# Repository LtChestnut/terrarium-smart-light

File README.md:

# terrarium-smart-light

An ESP32-based smart grow light for terrariums: a compact 56 mm round board with components on one side with full-spectrum white LEDs for plant growth, addressable RGB LEDs for effects, and Wi-Fi control.

## Features (planned)
- Seeed Studio XIAO module soldered directly to the board (ESP32-C6 recommended for its on-board antenna; the S3 and C3 also fit)
- Dimmable, wide-angle (120°) warm white LEDs (ams OSRAM DURIS E 2835, 3000 K, CRI 90+) on a constant-current boost driver (Legend-Si LGS63032EP, flicker-free PWM dimming)
- Addressable RGB pixels (WS2812-compatible) for sunrise/sunset, moonlight and effects
- A separate USB-C power port (5 V, works with any 2–3 A USB-C charger). The firmware reads the charger's advertised current and limits brightness to match
- 4-layer PCB with every component on one side (the back sits flat on a heatsink). JLCPCB Economic assembly places all LCSC parts; only the XIAO is hand-soldered
- Day/night schedule with sunrise and sunset ramps, a web UI, OTA updates, and Home Assistant via MQTT

## Repository layout
| Folder | Contents |
|---|---|
| [docs/](docs/) | Design plan ([docs/plan.md](docs/plan.md)) and research notes ([docs/research/](docs/research/)) |
| [hardware/](hardware/) | KiCad project, BOM, fabrication outputs |
| [firmware/](firmware/) | PlatformIO project for the XIAO (ESP32-C6 primary, S3 supported) |
| [enclosure/](enclosure/) | Enclosure STEP files exported from Onshape |

## Mechanical design
The enclosure is designed in Onshape: [Terrarium Smart Light enclosure (Onshape)](https://cad.onshape.com/documents/52f2a238255e278aeea46164/w/27e2eabc0946d9f68195188c/e/e4bc6922c2e565c6999771c4). The Onshape document is the source of truth; the STEP files in [enclosure/](enclosure/) are exports of it, so re-export them after changing the design.

| File | Part |
|---|---|
| [enclosure/main_enclosure.step](enclosure/main_enclosure.step) | Main enclosure body |
| [enclosure/frosted_window.step](enclosure/frosted_window.step) | Frosted window over the LEDs |

The PCB model used in the assembly is [hardware/Terrarium Smart Light.step](hardware/Terrarium%20Smart%20Light.step), exported from KiCad with `kicad-cli pcb export step --subst-models --no-optimize-step`. It mounts with the four M3 holes on the board edge.

## Status
PCB v0.6 has been sent for manufacture (JLCPCB); bring-up and firmware testing follow once boards arrive. The enclosure is designed in Onshape. See [docs/plan.md](docs/plan.md) for the architecture, power budget, BOM and open decisions.

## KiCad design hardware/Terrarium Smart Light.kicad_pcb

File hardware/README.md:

# Hardware

KiCad 10 project: `Terrarium Smart Light.kicad_pro`

| File | Contents |
|---|---|
| `Terrarium Smart Light.kicad_sch` | Root sheet: four hierarchical sheets wired together |
| `power_input.kicad_sch` | USB-C power-only sink (J1, SHOU HAN TYPE-C 6P), CC Rd resistors, XIAO feed diode |
| `mcu.kicad_sch` | Seeed XIAO ESP32-C6 (U1) |
| `white_led_driver.kicad_sch` | LGS63032EP boost driver (OVP divider at 31 V), 16 × OSRAM DURIS E 2835 3000 K CRI 90 (2 parallel strings of 8), NTC |
| `rgb_leds.kicad_sch` | 6 × XINGLIGHT XL-5050RGBW-2812B-HM addressable RGB chain, 2N7002 data level shifter |
| `libs/Terrarium_Smart_Light.kicad_sym` | Project symbols: Seeed_XIAO_ESP32C6, LGS63032EP |
| `libs/Terrarium_Smart_Light.pretty` | Project footprints: XIAO-ESP32-C6-SMD_EdgePads, LED_OSRAM_DURIS_E_2835, USB_C_Receptacle_SHOUHAN_TYPE-C-6P (LED_Seoul_SunLike_S1S0-3030 kept, unused) |
| `libs/Terrarium_Smart_Light.3dshapes` | Simplified 3D model for the OSRAM 2835 |
| `resources/` | XIAO STEP model, J1 drawing, `datasheets/` (PDFs; markdown copies in `docs/datasheets`) |
| `bom/bom.csv` | Master BOM (with `LCSC Part #`) |
| `bom/jlcpcb_bom.csv` | Parts for JLCPCB Economic assembly (LCSC numbers) |
| `bom/digikey_bom_5x.csv` | Hand-soldered parts for 5 boards (U1 only) |
| `fabrication-toolkit-options.json` | Saved Fabrication-Toolkit plugin options |
| `production/` | Fabrication-Toolkit output. **Not in git**: regenerate it for every order (see below) |

Checks:

```
kicad-cli sch erc "Terrarium Smart Light.kicad_sch"
kicad-cli pcb drc --schematic-parity --refill-zones "Terrarium Smart Light.kicad_pcb"
kicad-cli sch export bom -o bom/bom.csv --fields "Reference,Value,Footprint,Manufacturer,MFG Part Number,Supplier,Supplier Part Number,${QUANTITY}" --group-by "Value,MFG Part Number" "Terrarium Smart Light.kicad_sch"
```

## Generating production files (JLCPCB, Fabrication-Toolkit)

The [Fabrication-Toolkit](https://github.com/bennymeg/Fabrication-Toolkit) plugin builds everything JLCPCB needs from the board. It takes the gerbers, drill files, BOM and pick-and-place data straight from the PCB. It reads the **`LCSC Part #`** field on each footprint; every JLCPCB-placed part has one, while U1 (the XIAO, hand-soldered) and H1–H4 (holes) don't.

### 1. Install the plugin (once)
1. Open KiCad and go to **Tools → Plugin and Content Manager**.
2. Search for **Fabrication Toolkit**, click **Install**, then **Apply Pending Changes**.
3. Restart the PCB editor. A Fabrication Toolkit button appears in its top toolbar. It's also under **Tools → External Plugins**.

### 2. Before generating
1. **Update the PCB from the schematic** (F8), so the footprint fields (`LCSC Part #`, values) are current.
2. **Refill all zones** (press B).
3. **Run DRC** with "Test for parity between PCB and schematic" ticked. It should report 0 errors and 0 unconnected items. Silkscreen warnings are optional fixes.
4. **Save the board.**

### 3. Generate
1. Click the **Fabrication Toolkit** button.
2. The options saved in `fabrication-toolkit-options.json` are already right for this board:
   - **Auto fill:** on (refills zones first).
   - **Auto translate:** on (applies the plugin's JLCPCB rotation corrections).
   - **Exclude DNP:** off.
   - **Extra layers:** none.
3. Click **Generate**. The output goes to `hardware/production/`:

| File | Use |
|---|---|
| `Terrarium_Smart_Light.zip` | Gerbers and drill files, for the PCB order |
| `bom.csv` | Assembly BOM (LCSC part numbers) |
| `positions.csv` | Pick-and-place (CPL) file |
| `designators.csv`, `netlist.ipc` | Reference files. The IPC netlist can be uploaded for JLCPCB's electrical test |

### 4. Order on jlcpcb.com
**PCB:** upload `Terrarium_Smart_Light.zip` and set:
- **Layers:** 4.
- **Thickness:** 1.6 mm.
- **Stack-up:** JLC04161H-7628, which the DRC rules assume.
- **Via covering:** tented is fine. The 4-layer vias aren't via-in-pad filled (that's only free on 6+ layers), so leave "via-in-pad" off.
- **Edge plating / castellated holes:** none. The M3 edge holes are non-plated, which is what makes the board eligible for Economic assembly.

**PCB Assembly:** choose **Economic**, **top side**, and upload `bom.csv` and `positions.csv`. Then:
- **U1 (XIAO):** shows as unmatched, because it has no LCSC number. Leave it unplaced; it's soldered by hand.
- **Placement preview:** check every rotation, especially the 2835 LEDs and their polarity mark, the WS2812B pixels (pin 1), Q1 (SOT-23), D1/D2 (cathode bar), U2 (pin 1) and J1. If one is wrong, fix it in JLCPCB's preview, or add a rotation offset field on that footprint (see the plugin README) and regenerate.
- **Extended parts:** confirm stock in the quote. J1, U2, L1, RT1 and the LEDs are Extended; the rest are Basic.

Every order needs fresh output, which is why `production/` is in `.gitignore`.

The design rationale is in [../docs/plan.md](../docs/plan.md).

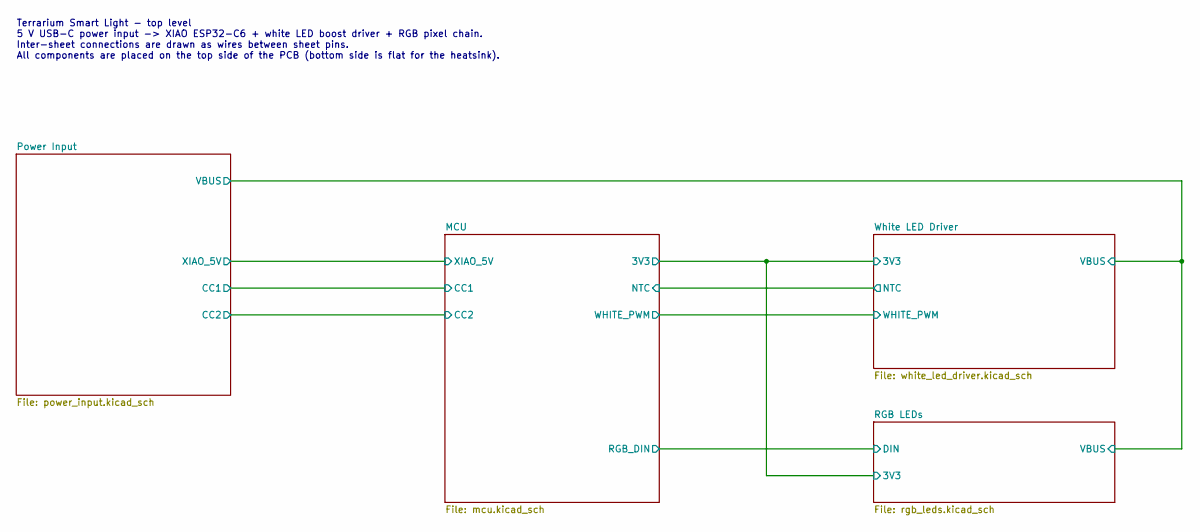
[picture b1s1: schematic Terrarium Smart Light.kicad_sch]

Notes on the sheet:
Terrarium Smart Light - top level 5 V USB-C power input -> XIAO ESP32-C6 + white LED boost driver + RGB pixel chain. Inter-sheet connections are drawn as wires between sheet pins. All components are placed on the top side of the PCB (bottom side is flat for the heatsink).

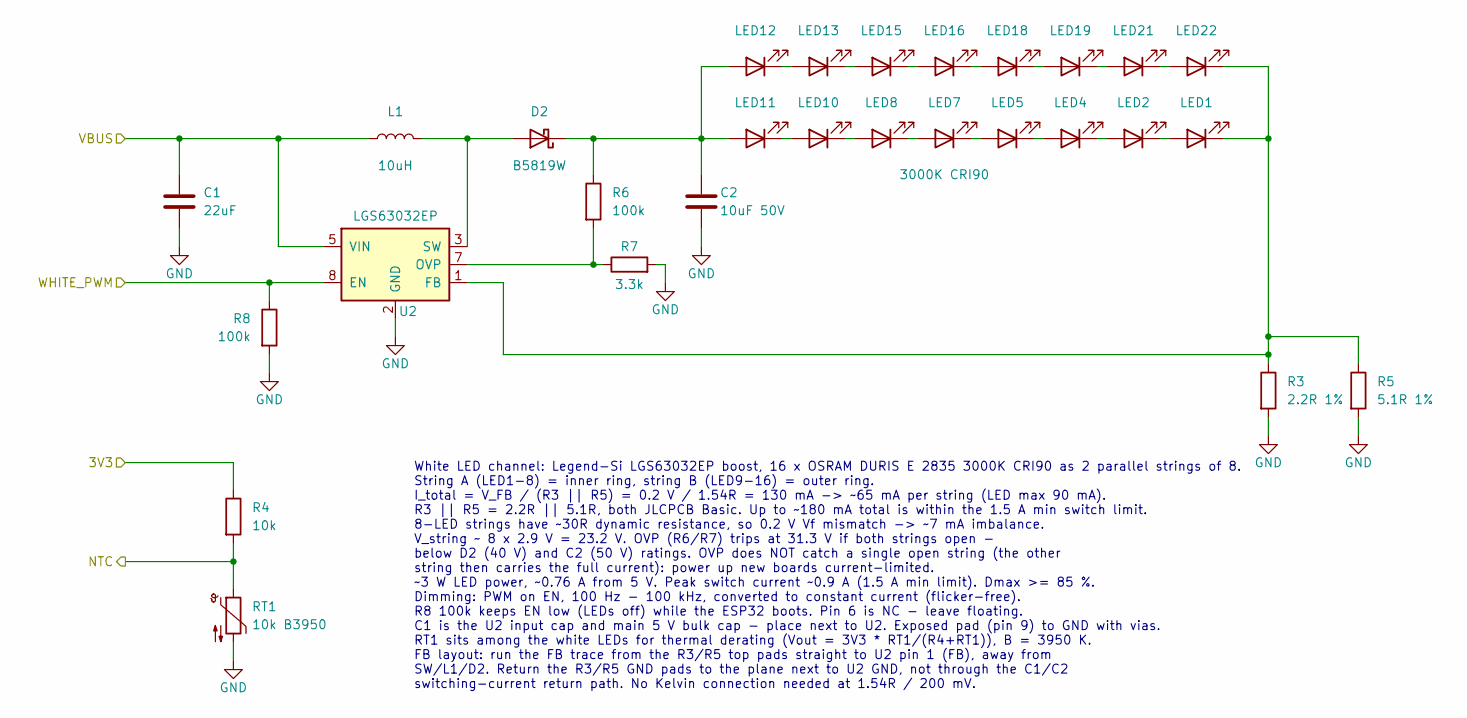
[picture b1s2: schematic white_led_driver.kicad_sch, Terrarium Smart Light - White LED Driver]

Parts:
C1: 22uF; C_1206_3216Metric; MFG Part Number CL31A226KAHNNNE; LCSC Part # C12891
C2: 10uF 50V; C_1206_3216Metric; MFG Part Number CL31A106KBHNNNE; LCSC Part # C13585
D2: B5819W; D_SOD-123; MFG Part Number B5819W SL; LCSC Part # C8598
L1: 10uH; L_Taiyo-Yuden_NR-40xx; MFG Part Number YNR4030-100M; LCSC Part # C340393
LED1, LED2, LED4, LED5, LED7, LED8, LED10, LED11, LED12, LED13, LED15, LED16, LED18, LED19, LED21, LED22: 3000K CRI90; LED_OSRAM_DURIS_E_2835; MFG Part Number GW JTLMS3.CM-G8GW-XX57-1-60-R33; LCSC Part # C30688624
R3: 2.2R 1%; R_0805_2012Metric; MFG Part Number 0805W8F220KT5E; LCSC Part # C17521
R4: 10k; R_0805_2012Metric; MFG Part Number 0805W8F1002T5E; LCSC Part # C17414
R5: 5.1R 1%; R_0805_2012Metric; MFG Part Number 0805W8F510KT5E; LCSC Part # C17724
R6, R8: 100k; R_0805_2012Metric; MFG Part Number 0805W8F1003T5E; LCSC Part # C149504
R7: 3.3k; R_0805_2012Metric; MFG Part Number 0805W8F3301T5E; LCSC Part # C26010
RT1: 10k B3950; R_0805_2012Metric; MFG Part Number CMFB103J3950HANT; LCSC Part # C338623
U2: LGS63032EP; SOIC-8-1EP_3.9x4.9mm_P1.27mm_EP2.41x3.3mm_ThermalVias; MFG Part Number LGS63032EP; LCSC Part # C5370937

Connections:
/MCU/3V3: R4.1; also elsewhere on the board
/MCU/NTC: R4.2, RT1.1; also elsewhere on the board
/MCU/WHITE_PWM: R8.1, U2.8 (EN); also elsewhere on the board
/Power Input/VBUS: C1.1, L1.1, U2.5 (VIN); also elsewhere on the board
GND: C1.2, C2.2, R3.2, R5.2, R7.2, R8.2, RT1.2, U2.2 (GND), U2.9 (EP); also elsewhere on the board
unnamed: D2.2 (A), L1.2, U2.3 (SW), U2.4 (SW)
unnamed: C2.1, D2.1 (K), LED11.2 (A), LED12.2 (A), R6.1
unnamed: LED1.2 (A), LED2.1 (K)
unnamed: LED1.1 (K), LED22.1 (K), R3.1, R5.1, U2.1 (FB)
unnamed: LED2.2 (A), LED4.1 (K)
unnamed: LED4.2 (A), LED5.1 (K)
unnamed: LED5.2 (A), LED7.1 (K)
unnamed: LED7.2 (A), LED8.1 (K)
unnamed: LED10.2 (A), LED11.1 (K)
unnamed: LED8.2 (A), LED10.1 (K)
unnamed: LED12.1 (K), LED13.2 (A)
unnamed: LED13.1 (K), LED15.2 (A)
unnamed: LED15.1 (K), LED16.2 (A)
unnamed: LED16.1 (K), LED18.2 (A)
unnamed: LED18.1 (K), LED19.2 (A)
unnamed: LED19.1 (K), LED21.2 (A)
unnamed: LED21.1 (K), LED22.2 (A)
unnamed: R6.2, R7.1, U2.7 (OVP)

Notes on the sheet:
White LED channel: Legend-Si LGS63032EP boost, 16 x OSRAM DURIS E 2835 3000K CRI90 as 2 parallel strings of 8. String A (LED1-8) = inner ring, string B (LED9-16) = outer ring. I_total = V_FB / (R3 || R5) = 0.2 V / 1.54R = 130 mA -> ~65 mA per string (LED max 90 mA). R3 || R5 = 2.2R || 5.1R, both JL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

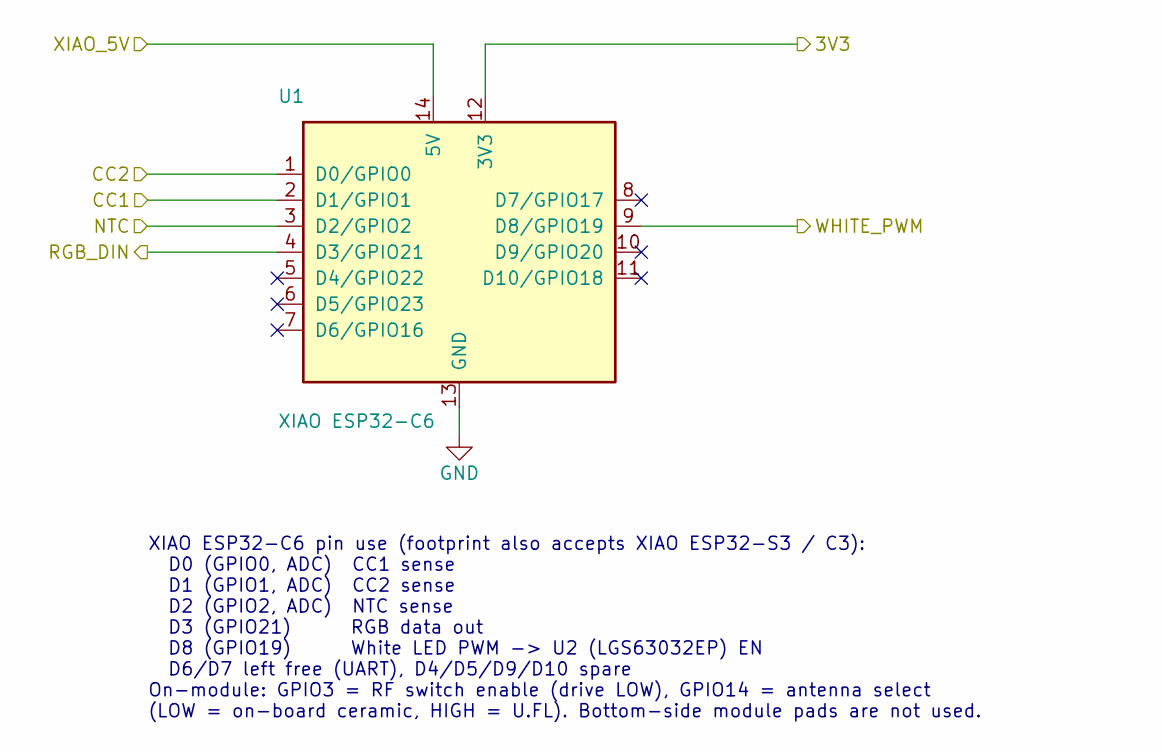
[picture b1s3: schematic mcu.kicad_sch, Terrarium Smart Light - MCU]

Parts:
U1: XIAO ESP32-C6; XIAO-ESP32-C6-SMD_EdgePads; MFG Part Number 113991254

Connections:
/MCU/3V3: U1.12 (3V3); also elsewhere on the board
/MCU/CC1: U1.2 (D1/GPIO1); also elsewhere on the board
/MCU/CC2: U1.1 (D0/GPIO0); also elsewhere on the board
/MCU/NTC: U1.3 (D2/GPIO2); also elsewhere on the board
/MCU/RGB_DIN: U1.4 (D3/GPIO21); also elsewhere on the board
/MCU/WHITE_PWM: U1.9 (D8/GPIO19); also elsewhere on the board
/MCU/XIAO_5V: U1.14 (5V); also elsewhere on the board
GND: U1.13 (GND); also elsewhere on the board

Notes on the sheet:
XIAO ESP32-C6 pin use (footprint also accepts XIAO ESP32-S3 / C3): D0 (GPIO0, ADC) CC1 sense D1 (GPIO1, ADC) CC2 sense D2 (GPIO2, ADC) NTC sense D3 (GPIO21) RGB data out D8 (GPIO19) White LED PWM -> U2 (LGS63032EP) EN D6/D7 left free (UART), D4/D5/D9/D10 spare On-module: GPIO3 = RF switch enable (d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

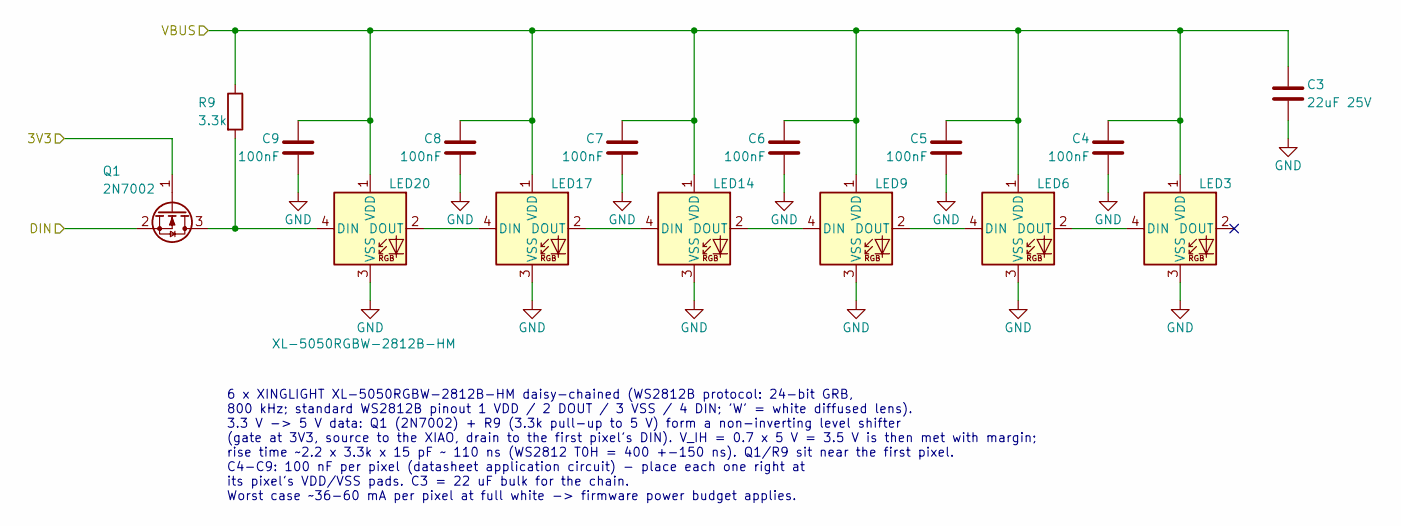
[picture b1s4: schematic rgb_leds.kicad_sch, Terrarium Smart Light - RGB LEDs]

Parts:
C3: 22uF 25V; C_1206_3216Metric; MFG Part Number CL31A226KAHNNNE; LCSC Part # C12891
C4, C5, C6, C7, C8, C9: 100nF; C_0603_1608Metric; MFG Part Number CC0603KRX7R9BB104; LCSC Part # C14663
LED3, LED6, LED9, LED14, LED17, LED20: XL-5050RGBW-2812B-HM; LED_WS2812B_PLCC4_5.0x5.0mm_P3.2mm; MFG Part Number XL-5050RGBW-2812B-HM; LCSC Part # C48586675
Q1: 2N7002; SOT-23; MFG Part Number 2N7002; LCSC Part # C8545
R9: 3.3k; R_0805_2012Metric; MFG Part Number 0805W8F3301T5E; LCSC Part # C26010

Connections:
/MCU/3V3: Q1.1 (G); also elsewhere on the board
/MCU/RGB_DIN: Q1.2 (S); also elsewhere on the board
/Power Input/VBUS: C3.1, C4.1, C5.1, C6.1, C7.1, C8.1, C9.1, LED3.1 (VDD), LED6.1 (VDD), LED9.1 (VDD), LED14.1 (VDD), LED17.1 (VDD), LED20.1 (VDD), R9.1; also elsewhere on the board
GND: C3.2, C4.2, C5.2, C6.2, C7.2, C8.2, C9.2, LED3.3 (VSS), LED6.3 (VSS), LED9.3 (VSS), LED14.3 (VSS), LED17.3 (VSS), LED20.3 (VSS); also elsewhere on the board
unnamed: LED3.4 (DIN), LED6.2 (DOUT)
unnamed: LED6.4 (DIN), LED9.2 (DOUT)
unnamed: LED14.4 (DIN), LED17.2 (DOUT)
unnamed: LED9.4 (DIN), LED14.2 (DOUT)
unnamed: LED17.4 (DIN), LED20.2 (DOUT)
unnamed: LED20.4 (DIN), Q1.3 (D), R9.2

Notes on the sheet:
6 x XINGLIGHT XL-5050RGBW-2812B-HM daisy-chained (WS2812B protocol: 24-bit GRB, 800 kHz; standard WS2812B pinout 1 VDD / 2 DOUT / 3 VSS / 4 DIN; 'W' = white diffused lens). 3.3 V -> 5 V data: Q1 (2N7002) + R9 (3.3k pull-up to 5 V) form a non-inverting level shifter (gate at 3V3, source to the XIAO,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

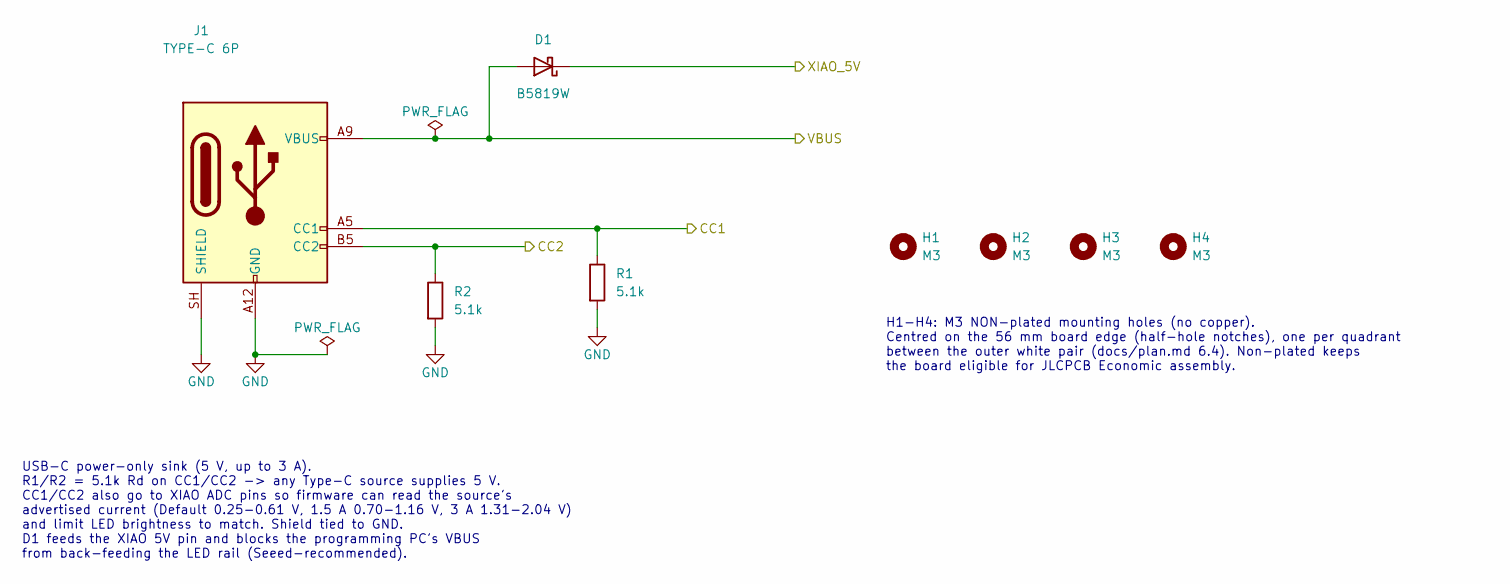
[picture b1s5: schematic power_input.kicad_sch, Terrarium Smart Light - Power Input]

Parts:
D1: B5819W; D_SOD-123; MFG Part Number B5819W SL; LCSC Part # C8598
H1, H2, H3, H4: M3; MountingHole_3.2mm_M3; MFG Part Number N/A
J1: TYPE-C 6P; USB_C_Receptacle_SHOUHAN_TYPE-C-6P; MFG Part Number TYPE-C 6P; LCSC Part # C456012
R1, R2: 5.1k; R_0805_2012Metric; MFG Part Number 0805W8F5101T5E; LCSC Part # C27834

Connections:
/MCU/CC1: J1.A5 (CC1), R1.1; also elsewhere on the board
/MCU/CC2: J1.B5 (CC2), R2.1; also elsewhere on the board
/MCU/XIAO_5V: D1.1 (K); also elsewhere on the board
/Power Input/VBUS: D1.2 (A), J1.A9 (VBUS), J1.B9 (VBUS); also elsewhere on the board
GND: J1.A12 (GND), J1.B12 (GND), J1.SH (SHIELD), R1.2, R2.2; also elsewhere on the board

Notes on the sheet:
H1-H4: M3 NON-plated mounting holes (no copper). Centred on the 56 mm board edge (half-hole notches), one per quadrant between the outer white pair (docs/plan.md 6.4). Non-plated keeps the board eligible for JLCPCB Economic assembly.
USB-C power-only sink (5 V, up to 3 A). R1/R2 = 5.1k Rd on CC1/CC2 -> any Type-C source supplies 5 V. CC1/CC2 also go to XIAO ADC pins so firmware can read the source's advertised current (Default 0.25-0.61 V, 1.5 A 0.70-1.16 V, 3 A 1.31-2.04 V) and limit LED brightness to match. Shield tied to GND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

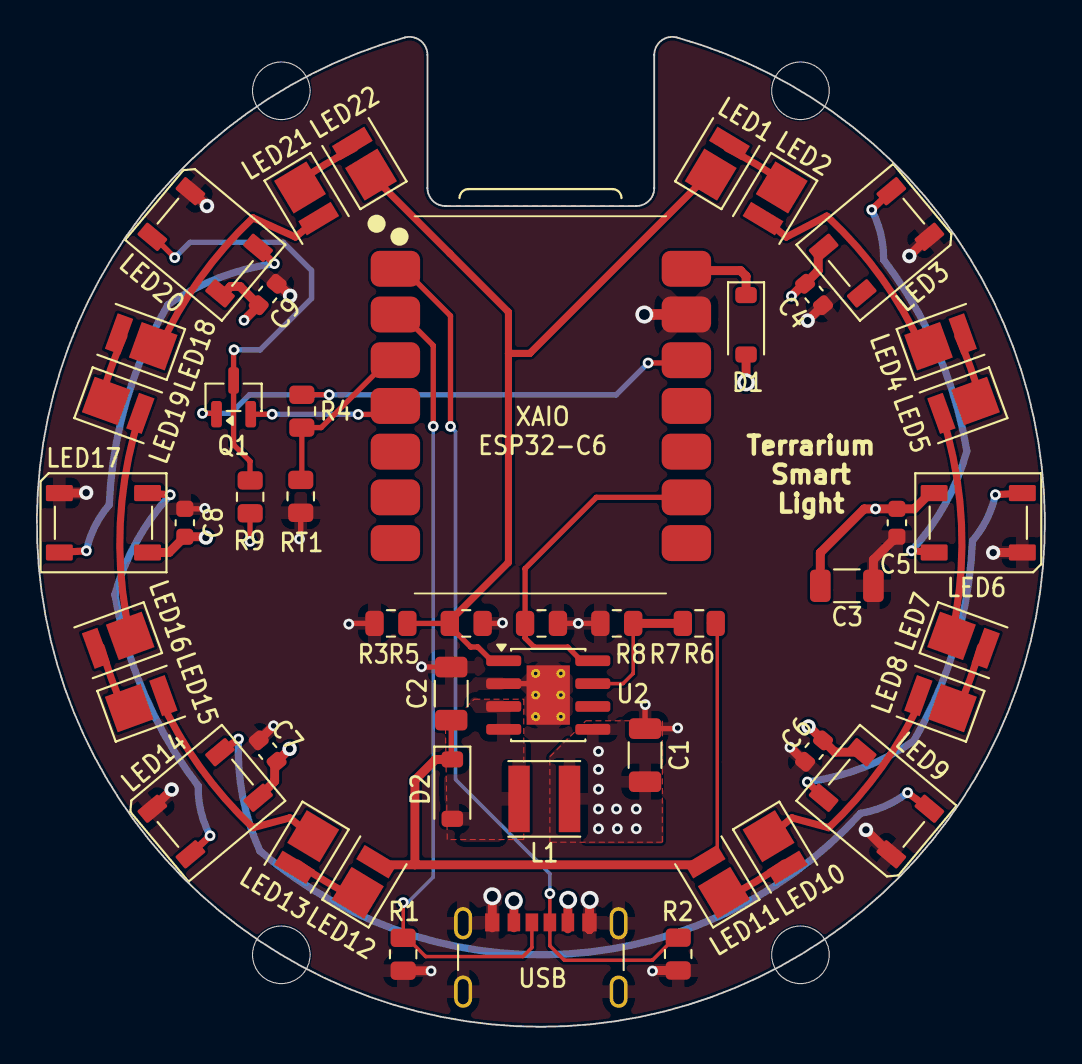
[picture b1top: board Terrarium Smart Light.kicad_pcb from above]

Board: 4 copper layers, 56.0 x 55.0 mm, 52 parts (0 on the bottom side), 33 nets.

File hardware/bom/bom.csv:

"Reference","Value","Footprint","Manufacturer","MFG Part Number","Supplier","Supplier Part Number","LCSC Part #","QUANTITY"
"C1,C3","22uF 25V","Capacitor_SMD:C_1206_3216Metric","Samsung Electro-Mechanics","CL31A226KAHNNNE","LCSC","C12891","C12891","2"
"C2","10uF 50V","Capacitor_SMD:C_1206_3216Metric","Samsung Electro-Mechanics","CL31A106KBHNNNE","LCSC","C13585","C13585","1"
"C4,C5,C6,C7,C8,C9","100nF","Capacitor_SMD:C_0603_1608Metric","YAGEO","CC0603KRX7R9BB104","LCSC","C14663","C14663","6"
"D1,D2","B5819W","Diode_SMD:D_SOD-123","JSCJ (Jiangsu Changjing)","B5819W SL","LCSC","C8598","C8598","2"
"J1","TYPE-C 6P","Terrarium_Smart_Light:USB_C_Receptacle_SHOUHAN_TYPE-C-6P","SHOU HAN","TYPE-C 6P","LCSC","C456012","C456012","1"
"L1","10uH","Inductor_SMD:L_Taiyo-Yuden_NR-40xx","YJYCOIN","YNR4030-100M","LCSC","C340393","C340393","1"
"LED1,LED2,LED4,LED5,LED7,LED8,LED10,LED11,LED12,LED13,LED15,LED16,LED18,LED19,LED21,LED22","3000K CRI90","Terrarium_Smart_Light:LED_OSRAM_DURIS_E_2835","ams OSRAM","GW JTLMS3.CM-G8GW-XX57-1-60-R33","LCSC","C30688624","C30688624","16"
"LED3,LED6,LED9,LED14,LED17,LED20","XL-5050RGBW-2812B-HM","LED_SMD:LED_WS2812B_PLCC4_5.0x5.0mm_P3.2mm","XINGLIGHT","XL-5050RGBW-2812B-HM","LCSC","C48586675","C48586675","6"
"R1,R2","5.1k","Resistor_SMD:R_0805_2012Metric","UNI-ROYAL","0805W8F5101T5E","LCSC","C27834","C27834","2"
"R3","2.2R 1%","Resistor_SMD:R_0805_2012Metric","UNI-ROYAL","0805W8F220KT5E","LCSC","C17521","C17521","1"
"R4","10k","Resistor_SMD:R_0805_2012Metric","UNI-ROYAL","0805W8F1002T5E","LCSC","C17414","C17414","1"
"R5","5.1R 1%","Resistor_SMD:R_0805_2012Metric","UNI-ROYAL","0805W8F510KT5E","LCSC","C17724","C17724","1"
"R6,R8","100k","Resistor_SMD:R_0805_2012Metric","UNI-ROYAL","0805W8F1003T5E","LCSC","C149504","C149504","2"
"Q1","2N7002","Package_TO_SOT_SMD:SOT-23","JSCJ (Jiangsu Changjing)","2N7002","LCSC","C8545","C8545","1"
"R7,R9","3.3k","Resistor_SMD:R_0805_2012Metric","UNI-ROYAL","0805W8F3301T5E","LCSC","C26010","C26010","2"
"RT1","10k B3950","Resistor_SMD:R_0805_2012Metric","FH (Guangdong Fenghua)","CMFB103J3950HANT","LCSC","C338623","C338623","1"
"U1","XIAO ESP32-C6","Terrarium_Smart_Light:XIAO-ESP32-C6-SMD_EdgePads","Seeed Studio","113991254","DigiKey","1597-113991254-ND","","1"
"U2","LGS63032EP","Package_SO:SOIC-8-1EP_3.9x4.9mm_P1.27mm_EP2.41x3.3mm","Legend-Si","LGS63032EP","LCSC","C5370937","C5370937","1"

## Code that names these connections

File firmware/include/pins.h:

// All GPIO assignments. Must match the schematic (hardware/mcu.kicad_sch) and the pin table
// in docs/plan.md section 6.5. The board only uses XIAO pins that exist on the C6, S3 and C3.
#pragma once

#include <sdkconfig.h>
#include <stdint.h>

//                                 XIAO pin   Net         Function
#if defined(CONFIG_IDF_TARGET_ESP32C6)
constexpr uint8_t PIN_CC1 = 0;        // D0     CC1         USB-C CC1 sense (ADC)
constexpr uint8_t PIN_CC2 = 1;        // D1     CC2         USB-C CC2 sense (ADC)
constexpr uint8_t PIN_NTC = 2;        // D2     NTC         Board thermistor (ADC)
constexpr uint8_t PIN_RGB_DIN = 21;   // D3     RGB_DIN     WS2812-style pixel data
constexpr uint8_t PIN_WHITE_PWM = 19; // D8     WHITE_PWM   LGS63032EP EN (PWM dimming)
// GPIO3 (RF switch enable, LOW) and GPIO14 (antenna select, LOW = on-board ceramic) are set
// by the XIAO_ESP32C6 variant's initVariant() before setup() runs.
#elif defined(CONFIG_IDF_TARGET_ESP32S3)
constexpr uint8_t PIN_CC1 = 1;
constexpr uint8_t PIN_CC2 = 2;
constexpr uint8_t PIN_NTC = 3;
constexpr uint8_t PIN_RGB_DIN = 4;
constexpr uint8_t PIN_WHITE_PWM = 7;
#elif defined(CONFIG_IDF_TARGET_ESP32C3)
// Fallback only: GPIO8 is a strapping pin (must be high at boot; the R8 EN pull-down
// fights it). There is no PlatformIO env for the C3.
constexpr uint8_t PIN_CC1 = 2;
constexpr uint8_t PIN_CC2 = 3;
constexpr uint8_t PIN_NTC = 4;
constexpr uint8_t PIN_RGB_DIN = 5;
constexpr uint8_t PIN_WHITE_PWM = 8;
#else
#error "Unsupported target: build for a XIAO ESP32-C6, S3 or C3"
#endif
